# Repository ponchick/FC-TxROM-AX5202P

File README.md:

# FC-TxROM-AX5202P

Cartridge PCB with an MMC3 mapper built around the AX5202P IC.

In theory, such a cartridge should support all TxROM-family board types. In practice, only the most common variants have been tested — no issues were found.

Russian version: [`README.ru.md`](README.ru.md)

## PRG RAM and battery support

The board supports PRG RAM for save data. A CR2032 cell retains data when the console is powered off.

- **If a battery is installed** (saves are required) — leave the **NO BATTERY** jumpers **open** (do not bridge them).
- **If no battery is used** (PRG RAM is on the board but saves are not needed) — bridge **both** **NO BATTERY** jumpers. PRG RAM is then powered from the console’s main supply, and data is lost when power is removed.

In no-battery mode, the following parts may be omitted:

- Battery BT1
- Resistors R1, R2, R3, R4
- Capacitors C4, C8
- Diodes D1, D2
- Transistor Q1

## CHR ROM / CHR RAM selection

Some games need RAM instead of ROM for pattern tables. Selection is done with three jumpers on the board:

- **CHR ROM mode** — bridge the upper pair of pads.
- **CHR RAM mode** — bridge the lower pair of pads.

## Mirror Control (mapper 118 support)

The two **MIRROR CONTROL** jumpers route `CHR A17` and `CIRAM A10`. This is required for correct operation of different TxROM board subtypes.

- **Upper position** — for mapper 118 (**TKSROM** and **TLSROM** boards).
- **Lower position** — for standard TxROM (e.g. **TKROM**, **TLROM**) and most other MMC3 games.

If you do not use mapper 118, keep the jumpers in the lower position.

## ROM type selection (pinout)

Two jumpers switch pins 1 and 31 of the ROM IC, because those pins differ between memory types.

- **Upper position** (`EEPROM/FLASH`) — for electrically erasable ROM (EEPROM) and FLASH.
- **Lower position** (`UV EPROM`) — for UV-erasable EPROM.

Set the jumpers to match the ROM you install.

## License

This project is licensed under **CERN Open Hardware Licence Version 2 – Permissive** (`CERN-OHL-P-2.0`).  
See `LICENSE` for details.

SPDX-License-Identifier: `CERN-OHL-P-2.0`

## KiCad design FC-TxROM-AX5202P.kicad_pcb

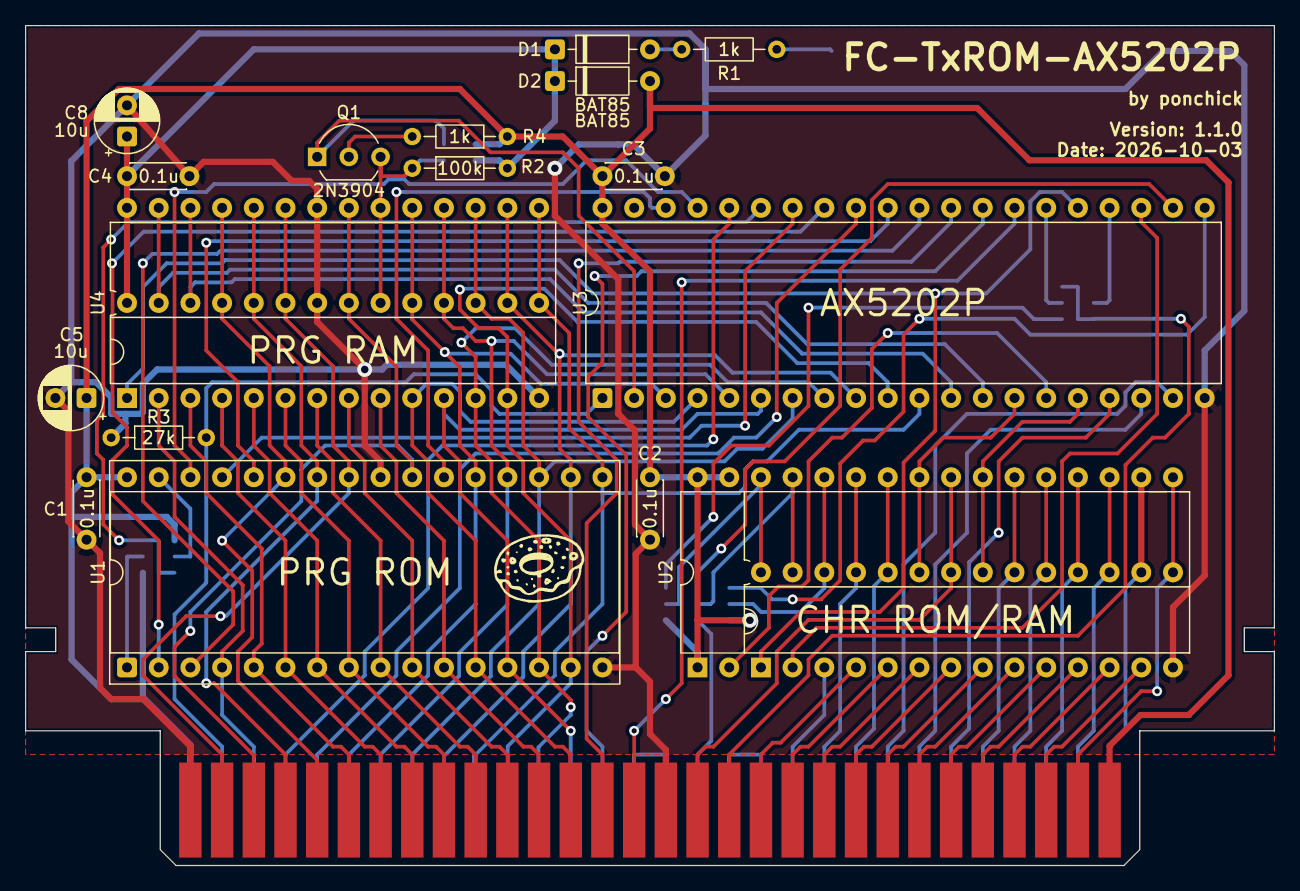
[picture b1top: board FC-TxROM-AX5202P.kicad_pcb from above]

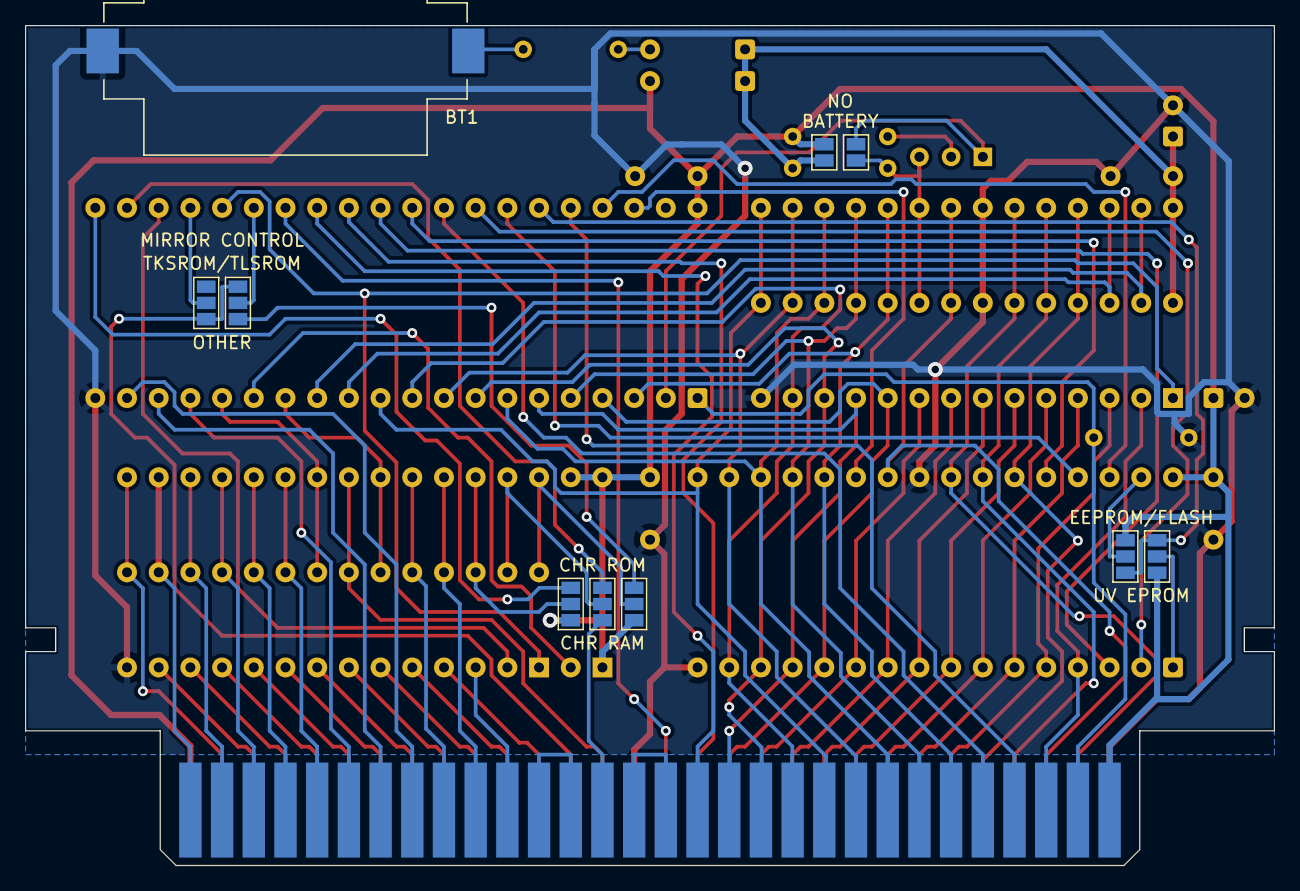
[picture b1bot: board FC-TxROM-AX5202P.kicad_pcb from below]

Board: 2 copper layers, 100.1 x 67.3 mm, 29 parts (10 on the bottom side), 86 nets.

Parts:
BT1: 2032; BatteryHolder_Keystone_1060_1x2032
C1, C2, C3, C4: 0.1u; C_Disc_D4.3mm_W1.9mm_P5.00mm
C5, C8: 10u; CP_Radial_D5.0mm_P2.50mm
D1, D2: BAT85; D_DO-35_SOD27_P7.62mm_Horizontal
J1: FAMICOM_EDGE; CONN_EDGE_2x60
JP1: +CE1 / A13; Jumper-3
JP2: ~{WE} / A14; Jumper-3
JP3, JP4: TKSROM/TLSROM/OTHER; Jumper-3
JP5: VDD / A17; Jumper-3
JP6, JP7: EPROM/FLASH; Jumper-3
JP8: UNSAFE_CE; SolderJumper-2_P1.3mm_Open_Pad1.0x1.5mm
JP9: SRAM_VCC; SolderJumper-2_P1.3mm_Open_Pad1.0x1.5mm
LOGO#: LOGO; ponchick
Q1: 2N3904; TO-92_Inline_Wide
R1, R4: 1k; R_Axial_DIN0204_L3.6mm_D1.6mm_P7.62mm_Horizontal
R2: 100k; R_Axial_DIN0204_L3.6mm_D1.6mm_P7.62mm_Horizontal
R3: 27k; R_Axial_DIN0204_L3.6mm_D1.6mm_P7.62mm_Horizontal
U1: PRG ROM; DIP-32_W15.24mm_Socket
U2: CHR ROM/RAM; DIP-32_Triple
U3: AX5202P; DIP-40_W15.24mm
U4: PRG RAM; DIP-28_Dual

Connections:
/CHR_A10: U2.23 (A10), U3.16 (CHR_A10)
/CHR_A11: U2.25 (A11), U3.14 (CHR_A11)
/CHR_A12: U2.4 (A12), U3.23 (CHR_A12)
/CHR_A13: JP1.1 (A), U3.21 (CHR_A13)
/CHR_A14: JP2.1 (A), U3.22 (CHR_A14)
/CHR_A15: U2.3 (A15), U3.25 (CHR_A15), U4.1 (NC)
/CHR_A16: U2.2 (A16), U3.15 (CHR_A16)
/CHR_A17: JP3.2 (C), U3.26 (CHR_A17)
/CHR_PIN26: JP1.2 (C), U2.28 (A13)
/CHR_PIN27: JP2.2 (C), U2.29 (A14)
/CHR_PIN28: JP5.2 (C), U2.30 (A17)
/CHR_PIN28_A17: JP3.3 (B), JP5.1 (A)
/CIRAM_A10: JP4.2 (C), U3.24 (CIRAM_A10)
/CPU_A0: J1.13 (CPU_A0), U1.12 (A0), U3.4 (CPU_A0), U4.10 (A0)
/CPU_A1: J1.12 (CPU_A1), U1.11 (A1), U4.9 (A1)
/CPU_A2: J1.11 (CPU_A2), U1.10 (A2), U4.8 (A2)
/CPU_A3: J1.10 (CPU_A3), U1.9 (A3), U4.7 (A3)
/CPU_A4: J1.9 (CPU_A4), U1.8 (A4), U4.6 (A4)
/CPU_A5: J1.8 (CPU_A5), U1.7 (A5), U4.5 (A5)
/CPU_A6: J1.7 (CPU_A6), U1.6 (A6), U4.4 (A6)
/CPU_A7: J1.6 (CPU_A7), U1.5 (A7), U4.3 (A7)
/CPU_A8: J1.5 (CPU_A8), U1.27 (A8), U4.25 (A8)
/CPU_A9: J1.4 (CPU_A9), U1.26 (A9), U4.24 (A9)
/CPU_A10: J1.3 (CPU_A10), U1.23 (A10), U4.21 (A10)
/CPU_A11: J1.2 (CPU_A11), U1.25 (A11), U4.23 (A11)
/CPU_A12: J1.33 (CPU_A12), U1.4 (A12), U4.2 (A12)
/CPU_A13: J1.34 (CPU_A13), U3.36 (CPU_A13)
/CPU_A14: J1.35 (CPU_A14), U3.32 (CPU_A14)
/CPU_D0: J1.43 (CPU_D0), U1.13 (D0), U3.6 (CPU_D0), U4.11 (Q0)
/CPU_D1: J1.42 (CPU_D1), U1.14 (D1), U3.8 (CPU_D1), U4.12 (Q1)
/CPU_D2: J1.41 (CPU_D2), U1.15 (D2), U3.10 (CPU_D2), U4.13 (Q2)
/CPU_D3: J1.40 (CPU_D3), U1.17 (D3), U3.11 (CPU_D3), U4.15 (Q3)
/CPU_D4: J1.39 (CPU_D4), U1.18 (D4), U3.9 (CPU_D4), U4.16 (Q4)
/CPU_D5: J1.38 (CPU_D5), U1.19 (D5), U3.7 (CPU_D5), U4.17 (Q5)
/CPU_D6: J1.37 (CPU_D6), U1.20 (D6), U3.5 (CPU_D6), U4.18 (Q6)
/CPU_D7: J1.36 (CPU_D7), U1.21 (D7), U3.3 (CPU_D7), U4.19 (Q7)
/CPU_RW: J1.14 (CPU_R/W), U3.29 (CPU_R/W)
/M2: J1.32 (M2), R3.2, U3.1 (M2)
/PPU_A0: J1.25 (PPU_A0), U2.12 (A0)
/PPU_A1: J1.24 (PPU_A1), U2.11 (A1)
/PPU_A2: J1.23 (PPU_A2), U2.10 (A2)
/PPU_A3: J1.22 (PPU_A3), U2.9 (A3)
/PPU_A4: J1.21 (PPU_A4), U2.8 (A4)
/PPU_A5: J1.20 (PPU_A5), U2.7 (A5)
/PPU_A6: J1.19 (PPU_A6), U2.6 (A6)
/PPU_A7: J1.50 (PPU_A7), U2.5 (A7)
/PPU_A8: J1.51 (PPU_A8), U2.27 (A8)
/PPU_A9: J1.52 (PPU_A9), U2.26 (A9)
/PPU_A10: J1.53 (PPU_A10), U3.19 (PPU_A10)
/PPU_A11: J1.54 (PPU_A11), U3.18 (PPU_A11)
/PPU_A12: J1.55 (PPU_A12), U3.17 (PPU_A12)
/PPU_A13: J1.56 (PPU_A13), U2.22 (CE)
/PPU_D0: J1.26 (PPU_D0), U2.13 (D0)
/PPU_D1: J1.27 (PPU_D1), U2.14 (D1)
/PPU_D2: J1.28 (PPU_D2), U2.15 (D2)
/PPU_D3: J1.29 (PPU_D3), U2.17 (D3)
/PPU_D4: J1.60 (PPU_D4), U2.18 (D4)
/PPU_D5: J1.59 (PPU_D5), U2.19 (D5)
/PPU_D6: J1.58 (PPU_D6), U2.20 (D6)
/PPU_D7: J1.57 (PPU_D7), U2.21 (D7)
/PRG_A13: U1.28 (A13), U3.31 (PRG_A13)
/PRG_A14: U1.29 (A14), U3.34 (PRG_A14)
/PRG_A15: U1.3 (A15), U3.30 (PRG_A15)
/PRG_A16: U1.2 (A16), U3.33 (PRG_A16)
/PRG_A17: U1.30 (A17), U3.37 (PRG_A17)
/PRG_A18: JP6.1 (A), JP7.3 (B), U3.35 (PRG_A18)
/PRG_PIN1: JP6.2 (C), U1.1 (A18)
/PRG_PIN31: JP7.2 (C), U1.31 (PGM)
/PRG_~CE: U1.22 (CE), U3.38 (PRG_~CE)
/VRAM_A10: J1.18 (CIRAM_A10), JP3.1 (A), JP4.3 (B)
/WRAM+CE: U3.12 (WRAM+CE), U4.26 (CS2)
/WRAM_SAFE_~CE: JP8.2 (B), Q1.3 (C), R2.1, U4.20 (~CS)
/WRAM_~CE: JP8.1 (A), Q1.1 (E), U3.2 (WRAM_~CE)
/WRAM_~WE: U3.13 (WRAM_~WE), U4.27 (~WE)
/~IRQ: J1.15 (~IRQ), U3.27 (~IRQ)
/~PPU_RD: J1.17 (~PPU_RD), U2.24 (OE)
/~PPU_WR: J1.47 (~PPU_WR), JP2.3 (B)
/~ROMSEL: J1.44 (~ROMSEL), U3.28 (~ROMSEL)
GND: BT1.2 (-), C1.2, C2.2, C3.2, C4.2, C5.2, C8.2, J1.1 (GND), J1.16 (GND), R3.1, U1.16 (GND), U1.24 (OE), U2.16 (GND), U3.20 (GND), U4.14 (GND), U4.22 (~OE)
unnamed: BT1.1 (+), R1.1
unnamed: D1.2 (A), R1.2
unnamed: J1.45 (AUDIO_IN), J1.46 (AUDIO_OUT)
unnamed: J1.48 (CIRAM_/CE), J1.49 (~PPU_A13)
unnamed: Q1.2 (B), R4.2
SRAM_VCC: C4.1, C8.1, D1.1 (K), D2.1 (K), JP9.2 (B), R2.2, U4.28 (VCC)
VCC: C1.1, C2.1, C3.1, C5.1, D2.2 (A), J1.30 (+5V), J1.31 (+5V), JP1.3 (B), JP5.3 (B), JP6.3 (B), JP7.1 (A), JP9.1 (A), R4.1, U1.32 (VCC), U2.1 (A18), U2.31 (PGM), U2.32 (VCC), U3.40 (VCC)

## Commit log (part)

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2026-05-03 Update BOM name format in ibom.config.ini to use forward slashes for directory structure
